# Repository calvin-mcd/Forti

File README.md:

# Førti

The Førti pcb (40 in Norwegian) is a 13u 40% pcb with full basekit support for the upcoming Førti keyboard case created and designed by xonuss and xezioh that is based on [Geon's F1-8x](https://geon.works/pages/f1-8x). The pcb takes its layout and design cues from the [oxymoron](https://imgur.com/a/UKyKxDe), [bully](https://www.cbkbd.com/product/bully) and [ttocyobitna](https://trashman.wiki/keyboards/ttocyobitna) amongst others. It's a stm32 based pcb for low cost, good performance.

## Layout

[Link](http://www.keyboard-layout-editor.com/#/gists/abf1199a554d2e1b5c349f9fdb908042)

## Case

WIP, design by xonuss

## Todo

- [X] order & test pcb
- [X] create firmware
- [X] order & test case
- [ ] revise mx pcb
- [ ] create HS & EC pcbs (work-in-progress)

## Disclaimer

Please note that this project is a work in progress with no guarantees of a working outcome. No-one involved in this project is responsible for any usage issues that may arise. However, feel free to edit, modify and otherwise utilise these files.

## License

Shield: 

This work is licensed under a  
[Creative Commons Attribution-NonCommercial-ShareAlike 4.0 International License](http://creativecommons.org/licenses/by-nc-sa/4.0/).

## Credits

Big thanks to xonuss and xezioh for letting me join this awesome collaboration!	

As always big thanks to the many people who helped and inspired this board!

Any questions, contact Calvin0563 on Discord.

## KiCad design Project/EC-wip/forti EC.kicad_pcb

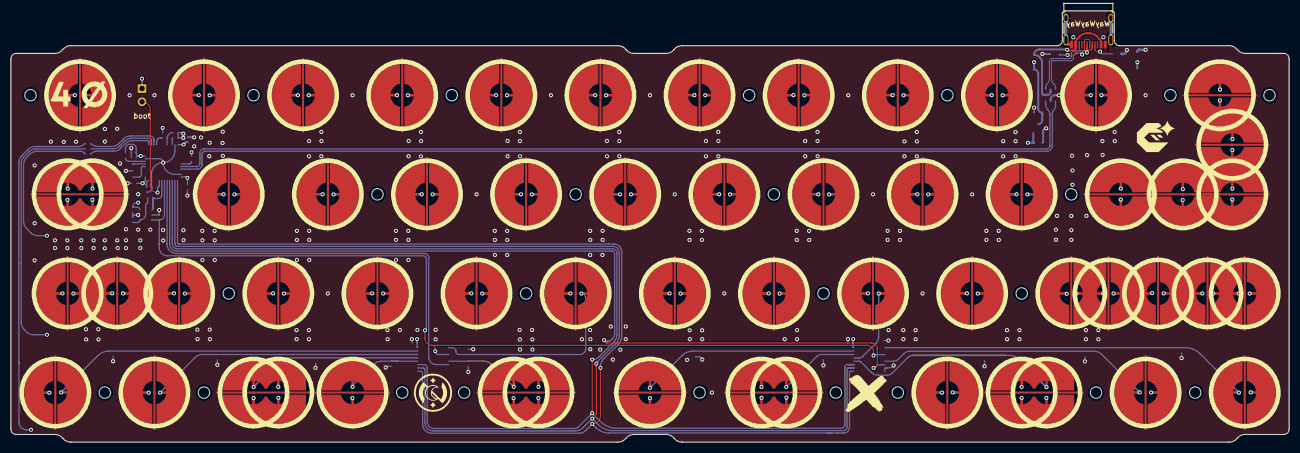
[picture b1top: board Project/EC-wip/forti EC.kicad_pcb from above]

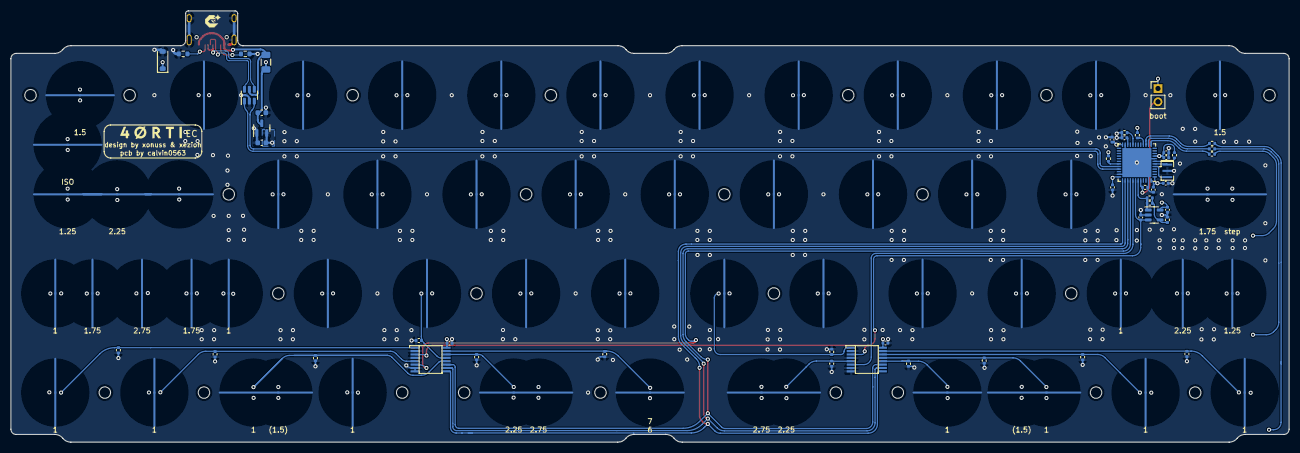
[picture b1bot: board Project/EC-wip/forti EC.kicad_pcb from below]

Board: 4 copper layers, 245.7 x 82.9 mm, 124 parts (48 on the bottom side), 45 nets.

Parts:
C1, C2: 1uF; C_0603_1608Metric
C3, C10, C15, C17, C18, C19, C20, C21: 100n; C_0402_1005Metric
C4: 220pF NP0; C_0402_1005Metric
C16: 4.7u; C_0402_1005Metric
C22: 1u; C_0402_1005Metric
D_PWR1: SMF9.0CA; D_SOD-123
F1: 500mA; Fuse_1206_3216Metric
H1, H2, H3, H4, H5, H6, H7, H8, H9, H10, H11, H12, H13, H14, H15, H16, H17, H18, H19, H20, H21, H22, H23, H24: MountingHole; HOLE_M2
J2: USB_C_Receptacle_USB2.0; USB_C_Receptacle_HRO_TYPE-C-31-M-12
R1, R2: 5k1; R_0603_1608Metric
R4, R5, R6, R7, R8, R9, R11, R12, R13, R14, R15, R16, R17, R18: 100k; R_0402_1005Metric
R19, R20, R21, R22: 100; R_0402_1005Metric
R23: 1k; R_0402_1005Metric
R24, R25, R27: 10k; R_0402_1005Metric
R26: DNP; R_0402_1005Metric
SW1: BOOT0; PinHeader_1x02_P2.54mm_Vertical
SW_EC1, SW_EC2, SW_EC3, SW_EC4, SW_EC5, SW_EC6, SW_EC7, SW_EC8, SW_EC9, SW_EC10, SW_EC11, SW_EC12, SW_EC14, SW_EC15, SW_EC16, SW_EC17, SW_EC18, SW_EC19, SW_EC20, SW_EC21, SW_EC22, SW_EC24, SW_EC25, SW_EC26, SW_EC27, SW_EC28, SW_EC29, SW_EC30, SW_EC31, SW_EC32, SW_EC33, SW_EC34, SW_EC50: Topre; ecs_pad_1U_no_ring
SW_EC13: stepped; ecs_pad_no_ring_stepped&normal
SW_EC23: Topre; ecs_pad_1U_no_ring_1u_edge_cut
SW_EC35, SW_EC36: 1u, 175u; ecs_pad_no_ring_1u1.75u
SW_EC37, SW_EC38, SW_EC40, SW_EC44, SW_EC46, SW_EC47: 1u; ecs_pad_1U_no_ring
SW_EC39, SW_EC45: stepped; ecs_pad_no_ring_stepped&normal_cut
SW_EC41, SW_EC43: split; ecs_pad_no_ring_stepped&normal
SW_EC42: 6u 7u; ecs_pad_1U_no_ring
SW_EC48: ISO; ecs_pad_1U_no_ring
SW_EC49: ansi; ecs_pad_1U_no_ring_1u_edge_cut
SW_EC52: 275u; ecs_pad_1U_no_ring
U1: USBLC6-2SC6; SOT-23-6
U2: XC6206PxxxMR-Regulator_Linear; SOT-23
U3: OPA354; SOT-23-5
U5, U7: 74HC4051; TSSOP16
U8: STM32F401CBUx; QFN-48-1EP_7x7mm_P0.5mm_EP5.6x5.6mm
Y1: 8 MHz; Resonator_SMD_Murata_CSTxExxV-3Pin_3.0x1.1mm

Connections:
+5V: C1.2, D_PWR1.1 (A1), F1.2, U2.3 (VI)
/CC1: J2.A5 (CC1), R1.1
/CC2: J2.B5 (CC2), R2.1
ADC: R6.1, R26.1, U3.1, U8.43 (PB7)
AMUX_SEL_0: U5.11 (S0), U7.11 (S0), U8.39 (PB3)
AMUX_SEL_1: U5.10 (S1), U7.10 (S1), U8.38 (PA15)
AMUX_SEL_2: U5.9 (S2), U7.9 (S2), U8.37 (PA14)
APLEX_EN_PIN_0: U5.6 (~E), U8.41 (PB5)
APLEX_EN_PIN_1: U7.6 (~E), U8.40 (PB4)
APLEX_OUT_PIN_0: C4.1, U3.3 (+), U5.3 (A), U7.3 (A), U8.42 (PB6)
BOOT0: R27.1, SW1.2 (B), U8.44 (BOOT0)
BOOT1: R25.2, U8.20 (PB2)
COL0: R7.1, SW_EC1.1, SW_EC13.1, SW_EC25.1, SW_EC37.1, SW_EC50.1, U5.15 (A2)
COL1: R5.1, SW_EC2.1, SW_EC14.1, SW_EC26.1, SW_EC38.1, U5.14 (A1)
COL2: R4.1, SW_EC3.1, SW_EC15.1, SW_EC27.1, SW_EC39.2, U5.13 (A0)
COL3: R8.1, SW_EC4.1, SW_EC16.1, SW_EC28.1, SW_EC40.1, U5.12 (A3)
COL4: R18.1, SW_EC5.1, SW_EC17.1, SW_EC29.1, SW_EC41.1, U5.5 (A5)
COL5: R9.1, SW_EC6.1, SW_EC18.1, SW_EC30.1, U5.1 (A4)
COL6: R13.1, SW_EC7.1, SW_EC19.1, SW_EC31.1, SW_EC42.1, U7.15 (A2)
COL7: R12.1, SW_EC8.1, SW_EC20.1, SW_EC32.1, SW_EC43.1, U7.14 (A1)
COL8: R11.1, SW_EC9.1, SW_EC21.1, SW_EC33.1, SW_EC44.1, U7.13 (A0)
COL9: R14.1, SW_EC10.1, SW_EC22.1, SW_EC34.1, SW_EC45.2, U7.12 (A3)
COL10: R16.1, SW_EC11.1, SW_EC23.2, SW_EC35.2, SW_EC46.1, U7.5 (A5)
COL11: R15.1, SW_EC12.1, SW_EC24.1, SW_EC36.1, SW_EC36.3, SW_EC47.1, SW_EC48.1, SW_EC49.1, SW_EC52.2, U7.1 (A4)
D_N: U1.3 (I/O2), U8.32 (PA11)
D_P: U1.1 (I/O1), U8.33 (PA12)
D_USB_N: J2.A7 (D-), J2.B7 (D-), U1.4 (I/O2)
D_USB_P: J2.A6 (D+), J2.B6 (D+), U1.6 (I/O1)
GND: C1.1, C2.1, C3.1, C4.2, C10.2, C15.2, C16.2, C17.2, C18.2, C19.2, C20.2, C21.2, C22.2, D_PWR1.2 (A2), J2.A1 (GND), J2.A12 (GND), J2.B1 (GND), J2.B12 (GND), J2.S1 (SHIELD), R1.2, R2.2, R4.2, R5.2, R7.2, R8.2, R9.2, R11.2, R12.2, R13.2, R14.2, R15.2, R16.2, R18.2, R23.2, R25.1, R27.2, SW_EC1.3 (SG), SW_EC2.3 (SG), SW_EC3.3 (SG), SW_EC4.3 (SG), SW_EC5.3 (SG), SW_EC6.3 (SG), SW_EC7.3 (SG), SW_EC8.3 (SG), SW_EC9.3 (SG), SW_EC10.3 (SG), SW_EC11.3 (SG), SW_EC12.3 (SG), SW_EC13.3 (SG), SW_EC14.3 (SG), SW_EC15.3 (SG), SW_EC16.3 (SG), SW_EC17.3 (SG), SW_EC18.3 (SG), SW_EC19.3 (SG), SW_EC20.3 (SG), SW_EC21.3 (SG), SW_EC22.3 (SG), SW_EC23.3 (SG), SW_EC24.3 (SG), SW_EC25.3 (SG), SW_EC26.3 (SG), SW_EC27.3 (SG), SW_EC28.3 (SG), SW_EC29.3 (SG), SW_EC30.3 (SG), SW_EC31.3 (SG), SW_EC32.3 (SG), SW_EC33.3 (SG), SW_EC34.3 (SG), SW_EC35.4 (SG), SW_EC36.4 (SG), SW_EC37.3 (SG), SW_EC38.3 (SG), SW_EC39.3 (SG), SW_EC40.3 (SG), SW_EC41.3 (SG), SW_EC42.3 (SG), SW_EC43.3 (SG), SW_EC44.3 (SG), SW_EC45.3 (SG), SW_EC46.3 (SG), SW_EC47.3 (SG), SW_EC48.3 (SG), SW_EC49.3 (SG), SW_EC50.3 (SG), SW_EC52.3 (SG), U1.2 (GND), U2.1 (GND), U3.2 (V-), U5.2 (A6), U5.4 (A7), U5.7 (VEE), U5.8 (GND), U7.2 (A6), U7.4 (A7), U7.7 (VEE), U7.8 (GND), U8.8 (VSSA), U8.23 (VSS), U8.35 (VSS), U8.47 (VSS), U8.49 (VSS), Y1.2
NRST: R24.2, U8.7 (NRST)
unnamed: R6.2, R23.1, R26.2, U3.4 (-)
unnamed: R19.1, U8.13 (PA3)
unnamed: R20.1, U8.14 (PA4)
unnamed: R21.2, U8.15 (PA5)
unnamed: R22.2, U8.16 (PA6)
unnamed: R17.1, U8.31 (PA10)
unnamed: C16.1, U8.22 (VCAP1)
ROW0: R22.1, SW_EC1.2, SW_EC2.2, SW_EC3.2, SW_EC4.2, SW_EC5.2, SW_EC6.2, SW_EC7.2, SW_EC8.2, SW_EC9.2, SW_EC10.2, SW_EC11.2, SW_EC12.2
ROW1: R19.2, SW_EC13.2, SW_EC14.2, SW_EC15.2, SW_EC16.2, SW_EC17.2, SW_EC18.2, SW_EC19.2, SW_EC20.2, SW_EC21.2, SW_EC22.2, SW_EC23.1, SW_EC24.2, SW_EC48.2, SW_EC49.2
ROW2: R20.2, SW_EC25.2, SW_EC26.2, SW_EC27.2, SW_EC28.2, SW_EC29.2, SW_EC30.2, SW_EC31.2, SW_EC32.2, SW_EC33.2, SW_EC34.2, SW_EC35.1, SW_EC35.3, SW_EC36.2, SW_EC50.2, SW_EC52.1
ROW3: R21.1, SW_EC37.2, SW_EC38.2, SW_EC39.1, SW_EC40.2, SW_EC41.2, SW_EC42.2, SW_EC43.2, SW_EC44.2, SW_EC45.1, SW_EC46.2, SW_EC47.2
VBAT: C2.2, C3.2, C10.1, C15.1, C17.1, C18.1, C19.1, C20.1, C21.1, C22.1, R17.2, R24.1, SW1.1 (A), U2.2 (VO), U3.5 (V+), U5.16 (VCC), U7.16 (VCC), U8.1 (VBAT), U8.9 (VREF+), U8.24 (VDD), U8.36 (VDD), U8.48 (VDD)
VBUS: F1.1, J2.A4 (VBUS), J2.A9 (VBUS), J2.B4 (VBUS), J2.B9 (VBUS), U1.5 (VBUS)
XTAL0: U8.5 (PH0), Y1.3
XTAL1: U8.6 (PH1), Y1.1

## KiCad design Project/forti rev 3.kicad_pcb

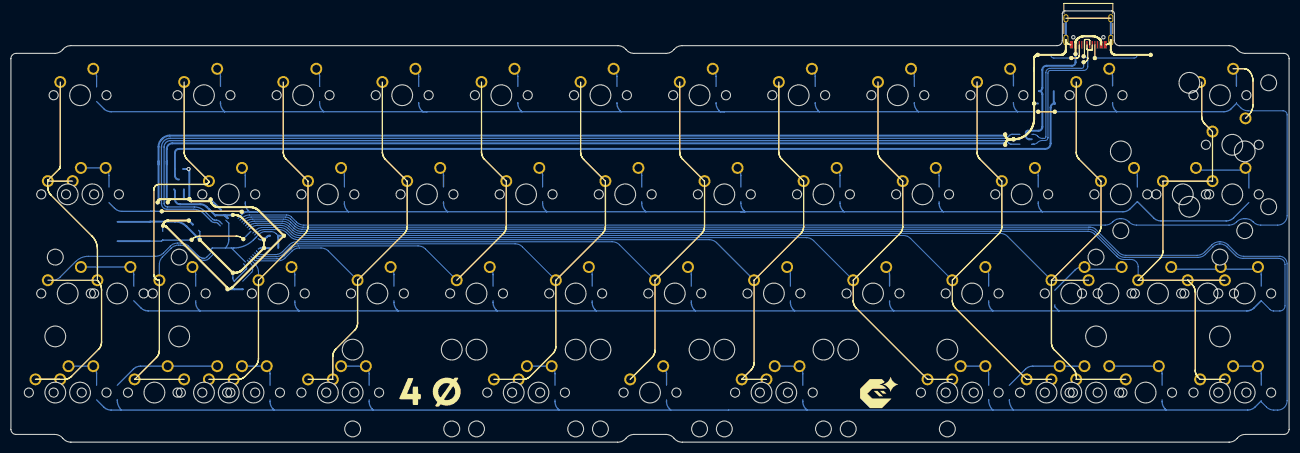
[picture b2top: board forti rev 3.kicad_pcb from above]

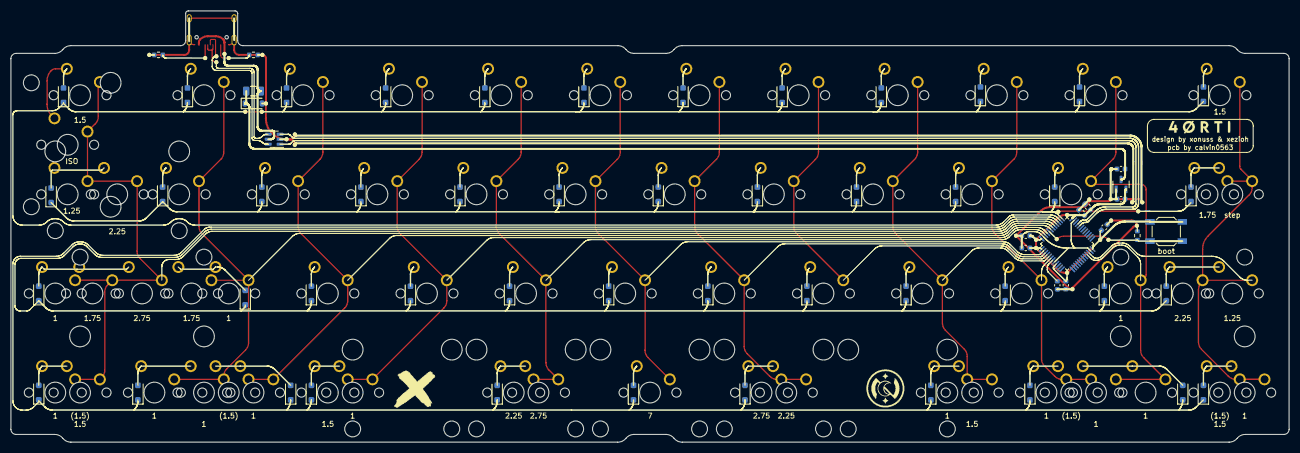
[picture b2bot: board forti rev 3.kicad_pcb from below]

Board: 2 copper layers, 245.7 x 82.9 mm, 139 parts (65 on the bottom side), 75 nets.

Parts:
C1, C2: 1uF; C_0603_1608Metric
C3: 10uF; C_0603_1608Metric
C4, C5, C6, C7, C8, C9: 100nF; C_0603_1608Metric
D1, D2, D3, D4, D5, D6, D7, D8, D9, D10, D11, D12, D13, D14, D15, D16, D17, D18, D19, D20, D21, D22, D23, D24, D25, D26, D27, D28, D29, D30, D31, D32, D33, D34, D35, D36, D37, D38, D39, D40, D41, D42, D43, D44, D45, D46, D47: D_Small; D_SOD-123F
D_PWR1: SMF9.0CA; D_SOD-123
F1: 500mA; Fuse_1206_3216Metric
ISO1: MX_stab; STAB_MX_ISO-ROT
J1: USB_C_Receptacle_USB2.0; USB_C_Receptacle_HRO_TYPE-C-31-M-12
MX1, MX12, MX40, MX44, MX46, MX49, MX51, MX55: MX_SW_HS; SW_MX_1.5u
MX2, MX3, MX4, MX5, MX6, MX7, MX8, MX9, MX10, MX11, MX14, MX15, MX16, MX17, MX18, MX19, MX20, MX21, MX22, MX23, MX26, MX27, MX28, MX29, MX30, MX31, MX32, MX33, MX34, MX35, MX38, MX39, MX41, MX42, MX43, MX45, MX47, MX48, MX50, MX52, MX53, MX54: MX_SW_HS; SW_MX_1u
MX13, MX36, MX37: MX_SW_HS; SW_MX_1.75u
MX24, MX25: MX_SW_HS; SW_MX_1.25u
MXISO1: MX_SW_HS; SW_MX_1u
MXcaps1: MX_SW_HS; SW_MX_1.75u_STP_1.25
MXenter2.1: MX_SW_HS; SW_MX_1u
MXshift2.1, MXshift2.2: MX_SW_HS; SW_MX_1u
MXsplit2.1, MXsplit2.2, MXsplit2.25(1)1, MXsplit2.75(1)1: MX_SW_HS; SW_MX_1u
R1, R2: 5k1; R_0603_1608Metric
R3: 10k; R_0603_1608Metric
S1, S4: 225; STAB_MX_2.25u
S2: 7; STAB_MX_7u
S3, S5: 275; STAB_MX_2.75u
SW1: SKQGABE010; SW_SPST_SKQG_WithoutStem
U1: USBLC6-2SC6; SOT-23-6
U2: STM32F072C8Tx; LQFP-48_7x7mm_P0.5mm
U3: XC6206PxxxMR-Regulator_Linear; SOT-23
enter2.1: MX_stab; STAB_MX_2.25u
shift2.1: MX_stab; STAB_MX_2.75u
shift2.2: MX_stab; STAB_MX_2.25u

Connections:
+3V3: C2.2, C3.1, C4.1, C5.1, C6.1, C7.1, C8.1, SW1.1, U2.1 (VBAT), U2.9 (VDDA), U2.24 (VDD), U2.36 (VDDIO2), U2.48 (VDD), U3.2 (VO)
+5V: C1.2, D_PWR1.1 (A1), F1.2, U3.3 (VI)
/CC1: J1.A5 (CC1), R1.1
/CC2: J1.B5 (CC2), R2.1
BOOT0: R3.1, SW1.2, U2.44 (BOOT0)
COL0: MX1.1, MX13.1, MX25.1, MX39.1, MX40.1, MXcaps1.1, MXshift2.1.1, U2.22 (PB11)
COL1: MX2.1, MX14.1, MX26.1, MX41.1, MX42.1, U2.21 (PB10)
COL2: MX3.1, MX15.1, MX27.1, MX43.1, MX44.1, U2.6 (PF1)
COL3: MX4.1, MX16.1, MX28.1, MX45.1, MX46.1, U2.5 (PF0)
COL4: MX5.1, MX17.1, MX29.1, U2.4 (PC15)
COL5: MX6.1, MX18.1, MX30.1, MXsplit2.1.1, MXsplit2.25(1)1.1, U2.3 (PC14)
COL6: MX7.1, MX19.1, MX31.1, MX47.1, U2.2 (PC13)
COL7: MX8.1, MX20.1, MX32.1, MXsplit2.2.1, MXsplit2.75(1)1.1, U2.46 (PB9)
COL8: MX9.1, MX21.1, MX33.1, MX48.1, MX49.1, U2.45 (PB8)
COL9: MX10.1, MX22.1, MX34.1, MX50.1, MX51.1, U2.43 (PB7)
COL10: MX11.1, MX23.1, MX35.1, MX36.1, MX52.1, MX53.1, U2.42 (PB6)
COL11: MX12.1, MX24.1, MX37.1, MX38.1, MX54.1, MX55.1, MXISO1.1, MXenter2.1.1, MXshift2.2.1, U2.41 (PB5)
D_N: U1.3 (I/O2), U2.32 (PA11)
D_P: U1.1 (I/O1), U2.33 (PA12)
D_USB_N: J1.A7 (D-), J1.B7 (D-), U1.4 (I/O2)
D_USB_P: J1.A6 (D+), J1.B6 (D+), U1.6 (I/O1)
GND: C1.1, C2.1, C3.2, C4.2, C5.2, C6.2, C7.2, C8.2, C9.2, D_PWR1.2 (A2), J1.A1 (GND), J1.A12 (GND), J1.B1 (GND), J1.B12 (GND), J1.S1 (SHIELD), R1.2, R2.2, R3.2, U1.2 (GND), U2.8 (VSSA), U2.23 (VSS), U2.35 (VSS), U2.47 (VSS), U3.1 (GND)
NRST: C9.1, U2.7 (NRST)
unnamed: D1.2 (A), MX1.2
unnamed: D2.2 (A), MX2.2
unnamed: D3.2 (A), MX3.2
unnamed: D4.2 (A), MX4.2
unnamed: D5.2 (A), MX5.2
unnamed: D6.2 (A), MX6.2
unnamed: D7.2 (A), MX7.2
unnamed: D8.2 (A), MX8.2
unnamed: D9.2 (A), MX9.2
unnamed: D10.2 (A), MX10.2
unnamed: D11.2 (A), MX11.2
unnamed: D12.2 (A), MX12.2, MXISO1.2
unnamed: D13.2 (A), MX13.2, MXcaps1.2
unnamed: D14.2 (A), MX14.2
unnamed: D15.2 (A), MX15.2
unnamed: D16.2 (A), MX16.2
unnamed: D17.2 (A), MX17.2
unnamed: D18.2 (A), MX18.2
unnamed: D19.2 (A), MX19.2
unnamed: D20.2 (A), MX20.2
unnamed: D21.2 (A), MX21.2
unnamed: D22.2 (A), MX22.2
unnamed: D23.2 (A), MX23.2
unnamed: D24.2 (A), MX24.2, MXenter2.1.2
unnamed: D25.2 (A), MX25.2, MXshift2.1.2
unnamed: D26.2 (A), MX26.2
unnamed: D27.2 (A), MX27.2
unnamed: D28.2 (A), MX28.2
unnamed: D29.2 (A), MX29.2
unnamed: D30.2 (A), MX30.2
unnamed: D31.2 (A), MX31.2
unnamed: D32.2 (A), MX32.2
unnamed: D33.2 (A), MX33.2
unnamed: D34.2 (A), MX34.2
unnamed: D35.2 (A), MX35.2, MX36.2
unnamed: D36.2 (A), MX37.2, MX38.2, MXshift2.2.2
unnamed: D37.2 (A), MX39.2, MX40.2
unnamed: D38.2 (A), MX41.2, MX42.2
unnamed: D39.2 (A), MX43.2, MX44.2
unnamed: D40.2 (A), MX45.2, MX46.2
unnamed: D41.2 (A), MXsplit2.1.2, MXsplit2.25(1)1.2
unnamed: D42.2 (A), MX47.2
unnamed: D43.2 (A), MXsplit2.2.2, MXsplit2.75(1)1.2
unnamed: D44.2 (A), MX48.2, MX49.2
unnamed: D45.2 (A), MX50.2, MX51.2
unnamed: D46.2 (A), MX52.2, MX53.2
unnamed: D47.2 (A), MX54.2, MX55.2
ROW0: D1.1 (K), D2.1 (K), D3.1 (K), D4.1 (K), D5.1 (K), D6.1 (K), D7.1 (K), D8.1 (K), D9.1 (K), D10.1 (K), D11.1 (K), D12.1 (K), U2.38 (PA15)
ROW1: D13.1 (K), D14.1 (K), D15.1 (K), D16.1 (K), D17.1 (K), D18.1 (K), D19.1 (K), D20.1 (K), D21.1 (K), D22.1 (K), D23.1 (K), D24.1 (K), U2.37 (PA14)
ROW2: D25.1 (K), D26.1 (K), D27.1 (K), D28.1 (K), D29.1 (K), D30.1 (K), D31.1 (K), D32.1 (K), D33.1 (K), D34.1 (K), D35.1 (K), D36.1 (K), U2.40 (PB4)
ROW3: D37.1 (K), D38.1 (K), D39.1 (K), D40.1 (K), D41.1 (K), D42.1 (K), D43.1 (K), D44.1 (K), D45.1 (K), D46.1 (K), D47.1 (K), U2.39 (PB3)
VBUS: F1.1, J1.A4 (VBUS), J1.A9 (VBUS), J1.B4 (VBUS), J1.B9 (VBUS), U1.5 (VBUS)

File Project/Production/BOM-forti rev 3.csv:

Comment,Designator,Footprint,LCSC,Quantity
SKQGABE010,SW1,SW_SPST_SKQG_WithoutStem,C115351,1
100nF,"C4,C5,C6,C7,C8,C9",C_0603_1608Metric,C14663,6
5k1,"R1,R2",R_0603_1608Metric,C14677,2
1uF,"C1,C2",C_0603_1608Metric,C15849,2
USB_C_Receptacle_USB2.0,J1,USB_C_Receptacle_HRO_TYPE-C-31-M-12,C165948,1
10k,R3,R_0603_1608Metric,C2139679,1
USBLC6-2SC6,U1,SOT-23-6,C2827654,1
XC6206PxxxMR-Regulator_Linear,U3,SOT-23,C5446,1
D_Small,"D1,D10,D11,D12,D13,D14,D15,D16,D17,D18,D19,D2,D20,D21,D22,D23,D24,D25,D26,D27,D28,D29,D3,D30,D31,D32,D33,D34,D35,D36,D37,D38,D39,D4,D40,D41,D42,D43,D44,D45,D46,D47,D5,D6,D7,D8,D9",D_SOD-123F,C64898,47
500mA,F1,Fuse_1206_3216Metric,C70076,1
SMF9.0CA,D_PWR1,D_SOD-123,C707469,1
STM32F072C8Tx,U2,LQFP-48_7x7mm_P0.5mm,C80488,1
10uF,C3,C_0603_1608Metric,C96446,1

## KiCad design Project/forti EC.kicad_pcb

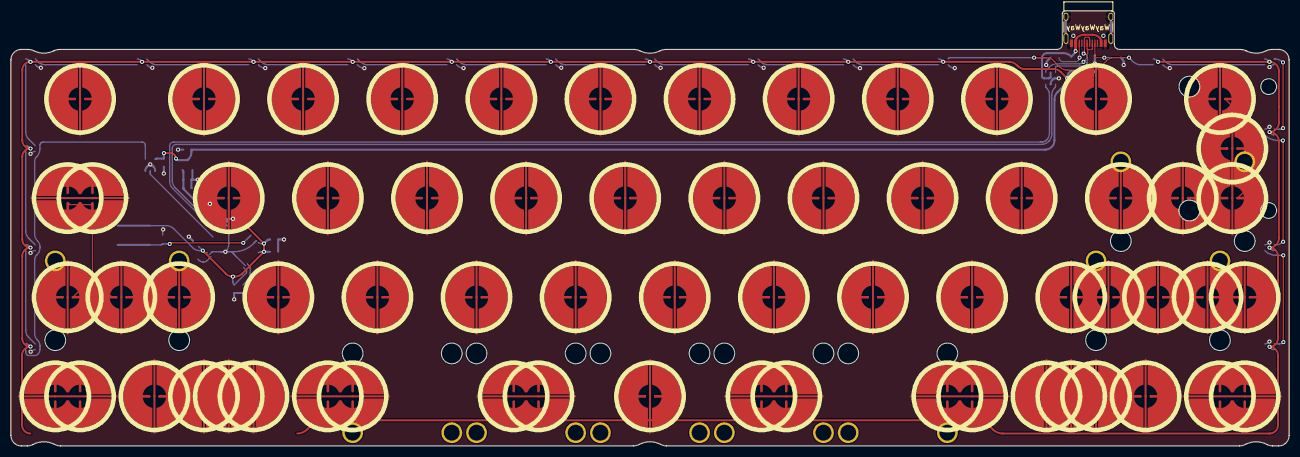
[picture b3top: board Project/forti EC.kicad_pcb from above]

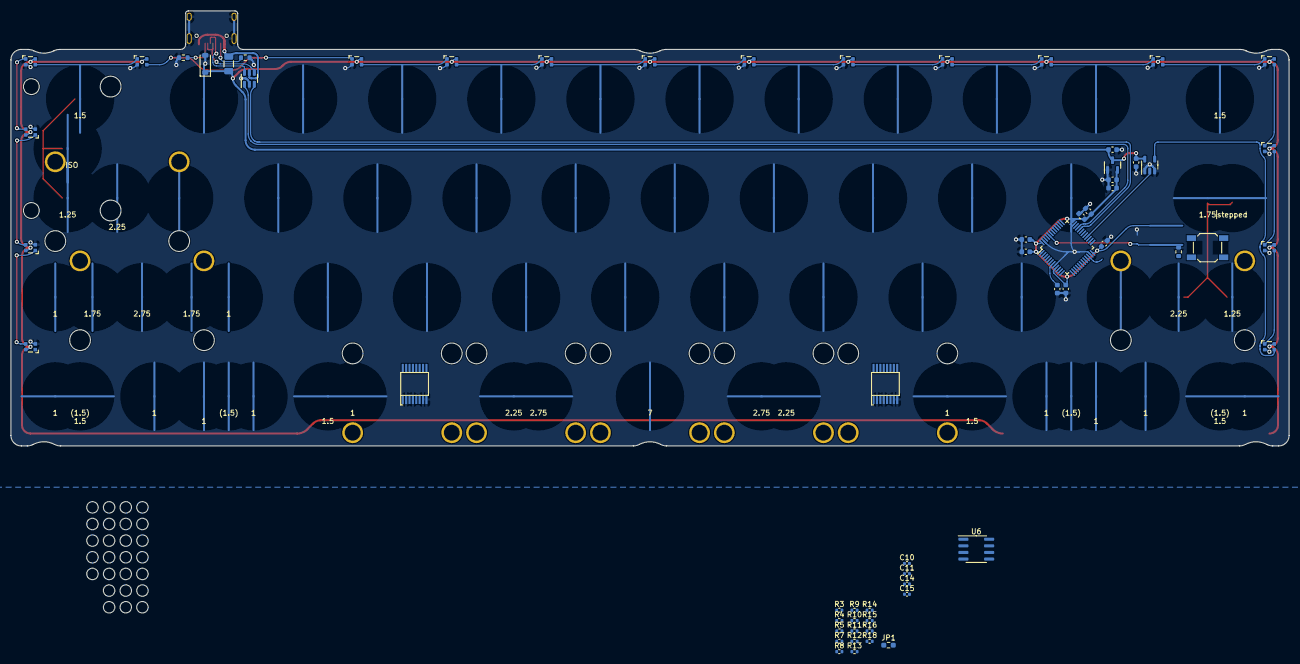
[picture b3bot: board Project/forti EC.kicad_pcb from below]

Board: 2 copper layers, 245.7 x 83.6 mm, 152 parts (61 on the bottom side), 53 nets.

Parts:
C1, C2, C4: 1uF; C_0603_1608Metric
C3: 4.7uF; C_0603_1608Metric
C5, C6, C7, C8, C9, C12, C13: 100nF; C_0603_1608Metric
C10, C14, C15: 100n; C_0402_1005Metric
C11: 220p; C_0402_1005Metric
D_PWR1: SMF9.0CA; D_SOD-123
F1: 500mA; Fuse_1206_3216Metric
H1, H2, H3, H4, H5, H6, H7, H8, H9, H10, H11, H12, H13, H14, H15, H16, H17, H18, H19, H20, H21, H22, H23, H24, H25, H26: MountingHole; HOLE_M2
ISO1: MX_stab; STAB_MX_ISO-ROT
J2: USB_C_Receptacle_USB2.0; USB_C_Receptacle_HRO_TYPE-C-31-M-12
JP1: Ext_Res; R_0603_1608Metric_Pad0.98x0.95mm_HandSolder
LED1, LED2, LED3, LED15, LED16, LED17, LED18, LED19, LED20, LED21, LED22, LED23, LED24, LED25, LED26, LED27, LED30, LED31: WS2812_2020; LED_WS2812_2020
R1, R2: 5k1; R_0603_1608Metric
R3, R4, R5, R7, R8, R9, R11, R12, R13, R14, R15, R16, R18: 100k; R_0402_1005Metric
R6: 10k; R_0603_1608Metric
R10: 1k; R_0402_1005Metric
S1: MX_stab; STAB_MX_P_7u
S2, S4: MX_stab; STAB_MX_P_2.25u
S3, S5: MX_stab; STAB_MX_P_2.75u
SW2: SKQGABE010; SW_SPST_SKQG_WithoutStem
SW_EC1, SW_EC2, SW_EC3, SW_EC4, SW_EC5, SW_EC6, SW_EC7, SW_EC8, SW_EC9, SW_EC10, SW_EC11, SW_EC12, SW_EC14, SW_EC15, SW_EC16, SW_EC17, SW_EC18, SW_EC19, SW_EC20, SW_EC21, SW_EC22, SW_EC23, SW_EC24, SW_EC25, SW_EC26, SW_EC27, SW_EC28, SW_EC29, SW_EC30, SW_EC31, SW_EC32, SW_EC33, SW_EC34, SW_EC42, SW_EC50: Topre; ecs_pad_1U_no_ring
SW_EC13, SW_EC37, SW_EC40, SW_EC44, SW_EC47: stepped; ecs_pad_no_ring_stepped&normal
SW_EC35: 1u; ecs_pad_no_ring_1u1.75u
SW_EC36: 175u; ecs_pad_no_ring_1u1.75u
SW_EC38, SW_EC39, SW_EC45, SW_EC46, SW_EC60, SW_EC61: 1u; ecs_pad_1U_no_ring
SW_EC41, SW_EC43: Topre; ecs_pad_no_ring_stepped&normal
SW_EC48: ISO; ecs_pad_1U_no_ring
SW_EC49: ansi; ecs_pad_1U_no_ring
SW_EC52: 275u; ecs_pad_1U_no_ring
SW_EC55, SW_EC58: 1.5u; ecs_pad_1U_no_ring
U1: USBLC6-2SC6; SOT-23-6
U2: XC6206PxxxMR-Regulator_Linear; SOT-23
U3: STM32F072C8Tx; LQFP-48_7x7mm_P0.5mm
U4: 74AHCT1G125; TSOT-23-5
U5, U7: 74HC4051; TSSOP16
U6: OPA350; SOIC-8_3.9x4.9mm_P1.27mm
enter2.25: MX_stab; STAB_MX_P_2.25u
shift2.25: MX_stab; STAB_MX_P_2.25u
shift2.75: MX_stab; STAB_MX_P_2.75u

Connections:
+3V3: C2.2, C3.1, C4.1, C5.1, C6.1, C7.1, C8.1, C9.1, C10.1, C14.1, C15.1, SW2.1, U2.2 (VO), U3.1 (VBAT), U3.9 (VDDA), U3.24 (VDD), U3.36 (VDDIO2), U3.48 (VDD), U5.16 (VCC), U6.7 (V+), U7.16 (VCC)
+5V: C1.2, C12.2, D_PWR1.1 (A1), F1.2, LED1.4 (VDD), LED2.4 (VDD), LED3.4 (VDD), LED15.4 (VDD), LED16.4 (VDD), LED17.4 (VDD), LED18.4 (VDD), LED19.4 (VDD), LED20.4 (VDD), LED21.4 (VDD), LED22.4 (VDD), LED23.4 (VDD), LED24.4 (VDD), LED25.4 (VDD), LED26.4 (VDD), LED27.4 (VDD), LED30.4 (VDD), LED31.4 (VDD), U2.3 (VI), U4.5 (VCC)
/CC1: J2.A5 (CC1), R1.1
/CC2: J2.B5 (CC2), R2.1
ADC: JP1.1 (A), R3.2, U6.6 (OUT)
AMUX_SEL_0: U5.11 (S0), U7.11 (S0)
AMUX_SEL_1: U5.10 (S1), U7.10 (S1)
AMUX_SEL_2: U5.9 (S2), U7.9 (S2)
APLEX_OUT_PIN_0: C11.2, U5.3 (A), U6.3 (IN+), U7.3 (A)
BOOT0: R6.1, SW2.2, U3.44 (BOOT0)
COL0: R7.1, SW_EC1.2, SW_EC13.2, SW_EC25.2, SW_EC37.2, SW_EC50.2, U3.22 (PB11), U5.15 (A2)
COL1: R5.1, SW_EC2.2, SW_EC14.2, SW_EC26.2, SW_EC38.2, SW_EC61.2, U3.21 (PB10), U5.14 (A1)
COL2: R4.1, SW_EC3.2, SW_EC15.2, SW_EC27.2, SW_EC39.2, SW_EC55.2, U3.6 (PF1), U5.13 (A0)
COL3: R8.1, SW_EC4.2, SW_EC16.2, SW_EC28.2, SW_EC40.2, U3.5 (PF0), U5.12 (A3)
COL4: R9.1, SW_EC5.2, SW_EC17.2, SW_EC29.2, SW_EC41.2, U3.4 (PC15), U5.1 (A4)
COL5: R18.1, SW_EC6.2, SW_EC18.2, SW_EC30.2, SW_EC42.2, U3.3 (PC14), U5.5 (A5)
COL6: R13.1, SW_EC7.2, SW_EC19.2, SW_EC31.2, SW_EC43.2, U3.2 (PC13), U7.15 (A2)
COL7: R12.1, SW_EC8.2, SW_EC20.2, SW_EC32.2, SW_EC44.2, U3.46 (PB9), U7.14 (A1)
COL8: R11.1, SW_EC9.2, SW_EC21.2, SW_EC33.2, SW_EC45.2, SW_EC58.2, U3.45 (PB8), U7.13 (A0)
COL9: R14.1, SW_EC10.2, SW_EC22.2, SW_EC34.2, SW_EC46.2, SW_EC60.2, U3.43 (PB7), U7.12 (A3)
COL10: R15.1, SW_EC11.2, SW_EC23.2, SW_EC35.2, SW_EC47.2, SW_EC52.2, U3.42 (PB6), U7.1 (A4)
COL11: R16.1, SW_EC12.2, SW_EC24.2, SW_EC36.2, SW_EC48.2, SW_EC49.2, U3.41 (PB5), U7.5 (A5)
D_N: U1.3 (I/O2), U3.32 (PA11)
D_P: U1.1 (I/O1), U3.33 (PA12)
D_USB_N: J2.A7 (D-), J2.B7 (D-), U1.4 (I/O2)
D_USB_P: J2.A6 (D+), J2.B6 (D+), U1.6 (I/O1)
GND: C1.1, C2.1, C3.2, C4.2, C5.2, C6.2, C7.2, C8.2, C9.2, C10.2, C11.1, C12.1, C13.2, C14.2, C15.2, D_PWR1.2 (A2), J2.A1 (GND), J2.A12 (GND), J2.B1 (GND), J2.B12 (GND), J2.S1 (SHIELD), LED1.2 (VSS), LED2.2 (VSS), LED3.2 (VSS), LED15.2 (VSS), LED16.2 (VSS), LED17.2 (VSS), LED18.2 (VSS), LED19.2 (VSS), LED20.2 (VSS), LED21.2 (VSS), LED22.2 (VSS), LED23.2 (VSS), LED24.2 (VSS), LED25.2 (VSS), LED26.2 (VSS), LED27.2 (VSS), LED30.2 (VSS), LED31.2 (VSS), R1.2, R2.2, R4.2, R5.2, R6.2, R7.2, R8.2, R9.2, R10.2, R11.2, R12.2, R13.2, R14.2, R15.2, R16.2, R18.2, SW_EC1.3, SW_EC2.3, SW_EC3.3, SW_EC4.3, SW_EC5.3, SW_EC6.3, SW_EC7.3, SW_EC8.3, SW_EC9.3, SW_EC10.3, SW_EC11.3, SW_EC12.3, SW_EC13.3, SW_EC14.3, SW_EC15.3, SW_EC16.3, SW_EC17.3, SW_EC18.3, SW_EC19.3, SW_EC20.3, SW_EC21.3, SW_EC22.3, SW_EC23.3, SW_EC24.3, SW_EC25.3, SW_EC26.3, SW_EC27.3, SW_EC28.3, SW_EC29.3, SW_EC30.3, SW_EC31.3, SW_EC32.3, SW_EC33.3, SW_EC34.3, SW_EC35.3, SW_EC36.3, SW_EC37.3, SW_EC38.3, SW_EC39.3, SW_EC40.3, SW_EC41.3, SW_EC42.3, SW_EC43.3, SW_EC44.3, SW_EC45.3, SW_EC46.3, SW_EC47.3, SW_EC48.3, SW_EC49.3, SW_EC50.3, SW_EC52.3, SW_EC55.3, SW_EC58.3, SW_EC60.3, SW_EC61.3, U1.2 (GND), U2.1 (GND), U3.8 (VSSA), U3.23 (VSS), U3.35 (VSS), U3.47 (VSS), U4.1, U4.3 (GND), U5.2 (A6), U5.4 (A7), U5.7 (VEE), U5.8 (GND), U6.4 (V-), U7.2 (A6), U7.4 (A7), U7.7 (VEE), U7.8 (GND)
NRST: C13.1, U3.7 (NRST)
unnamed: JP1.2 (B), R3.1, R10.1, U6.2 (IN-)
unnamed: LED1.3 (DIN), LED2.1 (DOUT)
unnamed: LED1.1 (DOUT), LED27.3 (DIN)
unnamed: LED2.3 (DIN), LED3.1 (DOUT)
unnamed: LED15.3 (DIN), LED16.1 (DOUT)
unnamed: LED16.3 (DIN), LED17.1 (DOUT)
unnamed: LED17.3 (DIN), LED18.1 (DOUT)
unnamed: LED18.3 (DIN), LED19.1 (DOUT)
unnamed: LED19.3 (DIN), LED20.1 (DOUT)
unnamed: LED20.3 (DIN), LED21.1 (DOUT)
unnamed: LED21.3 (DIN), LED22.1 (DOUT)
unnamed: LED22.3 (DIN), LED23.1 (DOUT)
unnamed: LED23.3 (DIN), LED30.1 (DOUT)
unnamed: LED24.3 (DIN), LED25.1 (DOUT)
unnamed: LED24.1 (DOUT), LED30.3 (DIN)
unnamed: LED25.3 (DIN), LED26.1 (DOUT)
unnamed: LED26.3 (DIN), LED31.1 (DOUT)
unnamed: LED27.1 (DOUT), LED31.3 (DIN)
RGB MCU: U3.28 (PB15), U4.2
ROW0: SW_EC1.1, SW_EC2.1, SW_EC3.1, SW_EC4.1, SW_EC5.1, SW_EC6.1, SW_EC7.1, SW_EC8.1, SW_EC9.1, SW_EC10.1, SW_EC11.1, SW_EC12.1, U3.38 (PA15)
ROW1: SW_EC13.1, SW_EC14.1, SW_EC15.1, SW_EC16.1, SW_EC17.1, SW_EC18.1, SW_EC19.1, SW_EC20.1, SW_EC21.1, SW_EC22.1, SW_EC23.1, SW_EC24.1, SW_EC48.1, SW_EC49.1, U3.37 (PA14)
ROW2: SW_EC25.1, SW_EC26.1, SW_EC27.1, SW_EC28.1, SW_EC29.1, SW_EC30.1, SW_EC31.1, SW_EC32.1, SW_EC33.1, SW_EC34.1, SW_EC35.1, SW_EC36.1, SW_EC50.1, SW_EC52.1, U3.40 (PB4)
ROW3: SW_EC37.1, SW_EC38.1, SW_EC39.1, SW_EC40.1, SW_EC41.1, SW_EC42.1, SW_EC43.1, SW_EC44.1, SW_EC45.1, SW_EC46.1, SW_EC47.1, SW_EC55.1, SW_EC58.1, SW_EC60.1, SW_EC61.1, U3.39 (PB3)
VBUS: F1.1, J2.A4 (VBUS), J2.A9 (VBUS), J2.B4 (VBUS), J2.B9 (VBUS), U1.5 (VBUS)
rgb underglow: LED3.3 (DIN), U4.4

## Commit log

2023-06-04 first full design
2023-06-05 backup
2023-06-07 slight routing cleanup
2023-06-09 component placement
2023-06-30 created 13u & 14u keyboard versions
2023-07-02 changed routing and reset button placement on 13u
2023-07-13 minimal gnd fill, added jst pico footprints
2023-08-05 routing update
2023-08-24 slight routing change, necessary?
2023-09-11 renaming project
2023-09-24 created production files
2023-10-01 fresh production files
2023-10-08 revision, small changes
2023-10-10 added images, update readme
2023-10-10 update license
2023-10-10 update readme, added production files
2023-10-10 fresh gerbers (small routing aeshetics)
2023-10-16 renamed project, moved HS into backup
2023-10-17 license update
2023-10-17 renamed HS backup
2023-10-22 new bottom row, proto project created, rgb revised
2023-10-29 updated bottom row options on solder, started HS, EC
2023-10-31 cleaned up main folder, created separate folder for different pcb versions
2023-11-09 EC progress
2023-11-17 progress on EC version
2023-12-02 small changes made after left shift was discovered to be wrong
    new new edge cut for full revision though
2024-01-14 EC bottom row and mounting holes
    need to double check routing 90°
2024-01-19 forti work
2024-01-28 backup / cleanup
2024-03-03 backups
2024-04-13 two different pcb versions
2024-04-21 forti gnd 2?
2024-04-22 gnd revision
2024-04-22 project cleanup
2024-05-05 usb revision
    no exposed copper yet
2024-06-07 rev 3
2024-12-22 revision
    usb needs fix still
2025-02-11 update production files v3
2025-02-23 rev 3 ready for proto
2025-05-09 rev 4
